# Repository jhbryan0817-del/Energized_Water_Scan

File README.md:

# Energized Water Scanner USV

A small unmanned surface vessel for research into detecting and mapping electrical hazards in flooded areas. Two deployable electrodes, E2/E4, measure voltage difference; the vessel must combine that measurement with validated probe pose, orientation and location. A low reading cannot establish that water is safe.

## Current state — 4 October 2026

**Electronics: Rev H engineering prototype. Mechanical assembly: live Fusion Rev I.** The PCB retains the 91 × 124 mm U-shaped perimeter, 58 × 48 mm motor opening, four mounting holes and 2 mm thickness. Six copper layers accommodate the revised electronics. The live Fusion assembly has been updated for Rev H placement, hull cleanup and corrective closure of obsolete bow/stern openings. Repository 3D exports remain historical; this update contains documentation and BOM changes only. See the [CAD audit](docs/CAD_Audit_2026-10-04.md) for verified results and remaining holds.

- [PCB design, operating limits and assembly](pcb/RevH/README.md)
- [Editable KiCad project](pcb/RevH/EWS_RevH.kicad_pro), [schematic PDF](pcb/RevH/EWS_RevH_schematic.pdf), [PCB BOM](pcb/RevH/BOM.csv), [connector pin map](pcb/RevH/PIN_MAP.md)
- [System design](docs/Design.md), [assembly and procurement](docs/Wiring_and_Assembly.md), [remaining qualification work](docs/Build_Qualification.md)
- [System BOM](BOM.csv): mechanical/harness items plus one assembled carrier. Components on that carrier are listed only in its PCB BOM.

Rev H adds a dedicated ADC per voltage range, hard-wired diagnostic/ready signals, reverse-input protection, a PCB-branch fuse and transient suppressor, battery monitoring and a dry-compartment ingress-sensor interface. The circuit targets sensitive measurements and a separate 600 V RMS, 50/60 Hz fault range. These are unqualified design targets. Bench calibration, insulation/protection review, physical fault testing and environmental qualification remain open. No validated acquisition firmware is supplied.

Historical Rev G previews and 3D exports are not the current mechanical authority. Use the saved live `Energized_Water_Scanner` Fusion document.

Two electrodes provide one field projection, not a full 3D field map or a direct measurement of floodwater current. Current-density estimates require independently measured conductivity and a valid field/geometry model. Fast transient measurement and an electrical-safety clearance decision are not released capabilities.

## Next milestones

1. Review the new PCB and validate components, protection, calibration, acquisition timing and fault behavior on a controlled bench.
2. Resolve the remaining mechanical holds in the CAD audit; verify actual components, wiring, seal compression and assembly tolerances.
3. Resolve actuator hardware and sealing, then test the unpowered hull for leakage and loaded flotation.
4. Implement and validate acquisition, invalid-state handling, pose/location logging and mapping; obtain appropriate laboratory qualification before hazardous exposure.

Detailed revision narratives and superseded preview images have been removed from the current documentation; Git history preserves them. Existing exported CAD releases are unchanged and superseded by the live Fusion assembly for this iteration. The `pcb/RevG` files are retained as the historical electrical baseline; use Rev H for new electronics work. Historical scripts and verification records retain their original scope and must not be treated as current acceptance evidence.

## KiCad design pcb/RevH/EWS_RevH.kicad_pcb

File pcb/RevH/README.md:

# Energized Water Scanner — PCB Rev H

**Engineering prototype, 3 October 2026.** Native KiCad 10 sources for the two-electrode flood-hazard research USV. Open `EWS_RevH.kicad_pro`. This revision changes electronics only. A subsequent 4 October live Fusion Rev I iteration updates the mechanical fit representation; see [CAD audit](../../docs/CAD_Audit_2026-10-04.md). No new STEP, F3D or STL was generated.

## What changed

- U4 at I2C address **0x48** acquires the high range. New U7 at **0x49** acquires the sensitive range. Both use AIN0–AIN1; each can run continuously at 860 samples/s nominal without alternating ranges. Their clocks are independent, so this is concurrent acquisition, not phase-synchronous sampling.
- Amplifier diagnostics and conversion-ready signals are routed to ESP32 inputs. No diagnostic fly-wires are needed. The existing expansion header still exposes these nets, but they are now reserved.
- J11 feeds F1, then a P-channel reverse-polarity MOSFET Q1. D5 suppresses positive transients on protected VBAT; D6 limits gate-source voltage. Added local rail capacitors supplement the regulator modules.
- A filtered 200 kΩ/33 kΩ battery divider, with 10 kΩ series and 100 nF at GPIO32, feeds ADC1 GPIO32. Its nominal ratio is 7.0606:1 (1.190 V at an 8.4 V battery), with an approximately 41.5 Hz pole. Select and calibrate the ESP32 ADC attenuation accordingly. J14 supports a dry-compartment, 3.3 V, open-drain ingress sensor on GPIO23. This is a powered sensor interface, not a pair of bare-water electrodes.
- Existing high-voltage divider networks, isolation packages, antenna restriction, U-shaped perimeter, motor opening and mounting holes are retained. The schematic, BOM and connector map describe the same board.

## Measurement capability and limits

E2 and E4 measure **signed differential voltage** along one probe separation. The DC-coupled analog circuit also permits AC measurements; initial AC qualification is for 50/60 Hz. These electrodes do not measure total current in floodwater. Under a validated locally uniform field model, the projected field is approximately `E_parallel = V / separation`. Estimating current density further requires conductivity, `J = conductivity × E`; total current also requires a defined area and field distribution. No conductivity sensor is included in this board. Use an independently isolated conductivity instrument if that quantity is needed; the ordinary I2C header is not an isolation barrier.

Two probes can miss a field perpendicular to their separation. A scan must include validated changes in orientation, accurate pose/time/location, immersion verification and invalid-data handling. Position/heading sensors can use the available 3.3 V I2C/UART interfaces; they are not fitted by this revision. DC electrode polarization, electrode material, fouling, contact impedance and motion-generated signals must be characterized separately from electronic DC response.

| Property | High range | Sensitive range |
|---|---:|---:|
| Series resistance per electrode leg | 4 × 249 kΩ | 4 × 249 kΩ |
| Sense resistance per leg | 1 kΩ | 100 kΩ |
| Ideal attenuation before isolation | 997:1 | 10.96:1 |
| Isolation-amplifier differential gain | 2 | 2 |
| Initial measurement target | 600 V RMS, 50/60 Hz; ±850 V DC engineering ceiling | ±2 V instantaneous |
| Initial ADS1115 PGA | ±2.048 V | ±0.512 V |
| Ideal electrode-referred code step | 31.16 mV | 85.63 µV |

These are design calculations, **not demonstrated accuracy, detection thresholds or exposure ratings**. The DC ceiling gives approximately the same divider stress as the crest of the AC target; continuous DC and wet electrochemistry still require separate validation. The low range intentionally clamps during a large fault. Do not use it until recovery has been characterized. PGA changes cannot recover a clipped amplifier signal or improve the amplifier's input offset.

Each differential ADC filter is 1 kΩ + 1 kΩ with 330 nF across the inputs: ideal pole 241 Hz. The ideal analog amplitude factors are approximately 0.979 at 50 Hz and 0.970 at 60 Hz. Include ADC digital-filter response, source loading, capacitor tolerance and temperature in calibration. Neither this pole nor the converter establishes broadband anti-alias performance. Fast impulses, arbitrary inverter spectra and high-frequency hazard characterization are not released capabilities.

At 600 V RMS, the ideal high-range AMC input is 0.851 V peak; its outputs remain approximately 0.589–2.291 V around the nominal 1.44 V common mode. Normal divider dissipation is about 22.5 mW per 249 kΩ resistor. Both channels together load the electrodes by about 1.044 MΩ before clamping and approximately 1 MΩ in a large fault. The source/electrode impedance can therefore produce substantial loading error. Per-resistor working voltage does not establish pulse withstand or a single-fault rating.

The AMC3330's specified input offset alone corresponds to about 0.299 V high-range or 3.29 mV sensitive-range electrode-referred error before calibration. Bias-current mismatch, clamp leakage, resistor matching, temperature and electrode effects add further error. A fine ADC code step is not proof of microvolt detection. Validate range overlap and retain separate calibration coefficients.

## Pin assignments

See [PIN_MAP.md](PIN_MAP.md) and `PIN_MAP.csv` for every connector pin.

| ESP32 GPIO | Rev H use |
|---|---|
| 36, input only | U4 high-range READY, active low; configure ADC conversion-ready mode |
| 35, input only | U7 sensitive-range READY, active low |
| 34, input only | U2 high-range DIAG, active low |
| 39, input only | U3 sensitive-range DIAG, active low |
| 32 / ADC1 | Battery health divider; calibrate ADC attenuation and gain |
| 23 | J14 ingress-sensor input; 10 kΩ pull-up, 1 kΩ series, 100 nF filter |
| 21 / 22 | SDA / SCL, 3.3 V I2C; addresses 0x48 and 0x49 reserved |
| 25 / 26 / 27 / 14 | E2 servo / E4 servo / steering / ESC control |

ADC AIN2 and AIN3 are grounded on each converter. They can support an occasional zero-input diagnostic during a deliberately invalidated acquisition interval. They are not available as general external analog inputs. J4 exposes both isolated-side analog pairs for service, and high READY/DIAG nets; low READY is also on J1 pin 6. Never connect anything on the floating electrode side to J4 or logic ground.

## Power and assembly

Use a **2S battery only**, 8.4 V maximum normal input. An external branch fuse near the battery remains necessary to protect its harness. F1 is a provisional 3 A fast fuse for the PCB branch; coordinate its interrupt rating and time-current curve with available fault current, inrush, connector ratings and measured loads. Motor/ESC propulsion current remains in its separate fused harness. F1 does not protect that harness.

Q1 is deliberately connected with **drain/tab to BAT_FUSED and source to protected VBAT**; reversing those connections defeats reverse-input blocking. At 2 A and the 10 mΩ room-temperature resistance limit quoted at −4.5 V gate drive, its calculated conduction loss is about 40 mW, before temperature increase. This is not a thermal qualification. It is not an ideal-diode controller and does not provide general backfeed isolation between powered sources.

D5 is a 12 V standoff SMBJ12A with a specified 19.9 V clamp at its rated test current. Actual overshoot, lead inductance, pulse energy and fuse coordination need testing. It is a battery-rail suppressor, not an electrode surge arrestor. Do not apply a sustained overvoltage or infer an automotive/load-dump rating. C40/C41/C42 are 25 V X5R parts; C41/C42 sit on 5 V outputs. Check effective capacitance under bias.

Keep combined servo load initially at or below the previous 2 A development limit, with a current-limited supply, and validate stall peaks and trace/via temperatures. Do not infer board current capacity from the D24V50F5 regulator name. New capacitors beneath U5/U6 require component height ≤1.35 mm and a measured ≥2 mm module standoff; check solder joints and module underside components too.

Disconnect the battery and remove JP1 before USB service. The ESP32 can be removed from its sockets. Battery monitoring is not an autonomous cell-balancing, undervoltage-cutoff or battery-management system. Do not leave the battery connected with the MCU supply deliberately removed: divider injection into an unpowered input has not been qualified. J14 is for short internal wiring to a compatible sensor; no exposed floodwater connection or external surge rating is provided. An absent sensor can resemble a dry condition and needs a pre-run functional check.

All GPIO are 3.3 V only. Retain a WROOM DevKitC V4. Flash pins remain unavailable; boot-strapping restrictions still apply to the remaining expansion pins. U5/U6 control pins at J9 are VIN-referenced, not direct GPIO interfaces. Leave the ESC BEC lead disconnected and insulated. Never parallel the regulator outputs.

## Mechanical interface

Six copper layers, 2 mm thickness, 91 × 124 mm overall. Fusion coordinates: X −20…71, Y −62…62 mm. Motor opening: X 13…71, Y −24…24 mm. Four Ø3.4 mm holes: (−17,−58.5), (67,−58.5), (−17,58.5), (67,58.5). KiCad X = Fusion X + 50; KiCad Y = 100 − Fusion Y.

Retain the Rev G 1 mm nylon spacer arrangement, subject to actual screw engagement and underside solder-tail clearance. The existing outline and hole geometry are checked against the previous board. Populated heights, leads, connectors, ESC attachment and hatch clearance must be checked in the next Fusion iteration and on real hardware. The populated fit representation is maintained only in the live Fusion document; it is not a supplier-certified assembly or a manufacturing export.

The nominal six-layer stack uses 70 µm outer and 35 µm inner copper, dielectric layers 0.20/0.30/0.70/0.30/0.20 mm, and 0.01 mm mask per side. It totals 2.00 mm. The fabricator must confirm materials, pressed thickness, tolerances and insulation requirements. No controlled impedance is claimed. The added layers provide space through the restricted neck without reducing the input-isolation rules.

## Verification and next work

**Final automated results: zero ERC violations, zero DRC violations, zero unrouted connections and zero schematic parity issues.** A separate schematic-netlist/board/manifest comparison matched 319 connected pins. Exact Edge.Cuts geometry and the four mounting holes match Rev G. `ERC.json`, `DRC.json`, `verification.json` and `calculations.json` record the checks actually performed. ERC/DRC cannot validate a circuit topology, component derating, electrode performance or electrical safety. Custom copper rules retain the prior 8 mm floating-input-to-logic target and graded internal divider spacing. They do not derive creepage, installation category, pollution degree, laminate CTI or wet-insulation compliance.

Before hazardous exposure, obtain a qualified insulation/protection review and laboratory verification of common-mode and differential exposure, surges, single faults, resistor failures, clamp leakage/recovery, humidity/contamination, dielectric withstand, lead/enclosure insulation and thermal limits. Establish actual sensitivity and calibrated bandwidth using isolated, current-limited laboratory sources. Do not test in occupied energized water. A low reading, broken lead, dry probe, stalled conversion or saturated channel must never be interpreted as safe water.

Firmware is deferred. Its contract is: configure both converters explicitly; timestamp each ready event; detect stale data, clipping, DIAG faults, startup and recovery; invalidate health failures; calculate DC and AC quantities separately; log pose/location and uncertainty. No minimum detectable field or alarm threshold is released.

## Primary references

- [TI AMC3330](https://www.ti.com/lit/ds/symlink/amc3330.pdf): isolated amplifier limits, input/output behavior and supply network.
- [TI ADS1115](https://www.ti.com/lit/ds/symlink/ads1115.pdf): PGA, MUX, I2C addressing and conversion-ready timing.
- [Diodes DMPH3010LK3](https://www.diodes.com/datasheet/download/DMPH3010LK3.pdf): MOSFET pinout and ratings.
- [Littelfuse SMBJ](https://m.littelfuse.com/~/media/electronics/datasheets/tvs_diodes/littelfuse_tvs_diode_smbj_datasheet.pdf.pdf) and [451/453 fuse series](https://www.littelfuse.com/~/media/electronics/datasheets/fuses/littelfuse_fuse_451_453_datasheet.pdf.pdf).
- [Espressif DevKitC V4](https://docs.espressif.com/projects/esp-dev-kits/en/latest/esp32/esp32-devkitc/user_guide.html), [Pololu logic module](https://www.pololu.com/product/2831), [Pololu servo module](https://www.pololu.com/product/2851).

Native files were edited through KiCad's pcbnew API and checked with kicad-cli 10.0.6. The local IPC server answered the version query but returned no open-document handler. No claim of live IPC board editing or physical testing is made.

The native schematic uses project-local functional pin-map symbols with named global nets, continuing the previous project style. It is electrically editable and checked for board parity; it is not a substitute for an independent circuit review. No new fabrication order or manufacturing release is authorized by these reports.

Checks use the configured project rules. The reports list inherited ignored checks, including missing courtyards, track-to-via centering and footprint filters. No new violation was excluded to obtain the result. Mechanical fit of parts above sockets or module standoffs remains a separate check. The archive intentionally excludes 3D models; references inherited from Rev G are represented in the live Fusion fit assembly, with provisional envelopes identified in the CAD audit.

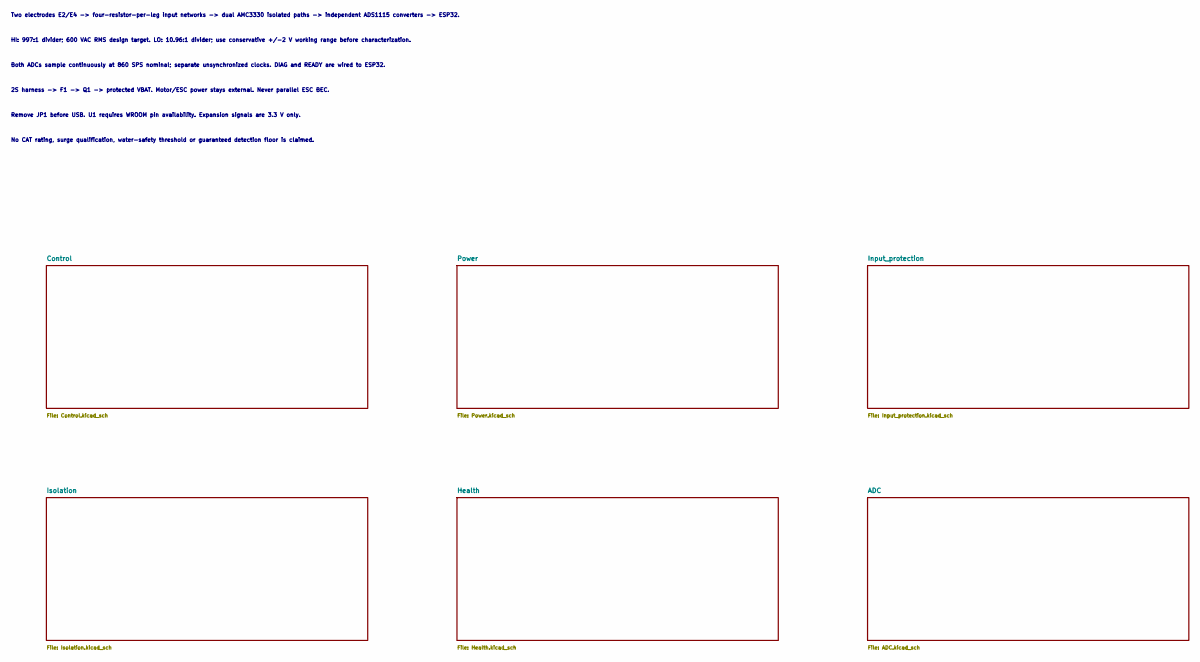
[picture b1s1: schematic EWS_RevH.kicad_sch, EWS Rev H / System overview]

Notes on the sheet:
Two electrodes E2/E4 -> four-resistor-per-leg input networks -> dual AMC3330 isolated paths -> independent ADS1115 converters -> ESP32.
HI: 997:1 divider; 600 VAC RMS design target. LO: 10.96:1 divider; use conservative +/-2 V working range before characterization.
Both ADCs sample continuously at 860 SPS nominal; separate unsynchronized clocks. DIAG and READY are wired to ESP32.
2S harness -> F1 -> Q1 -> protected VBAT. Motor/ESC power stays external. Never parallel ESC BEC.
Remove JP1 before USB. U1 requires WROOM pin availability. Expansion signals are 3.3 V only.
No CAT rating, surge qualification, water-safety threshold or guaranteed detection floor is claimed.

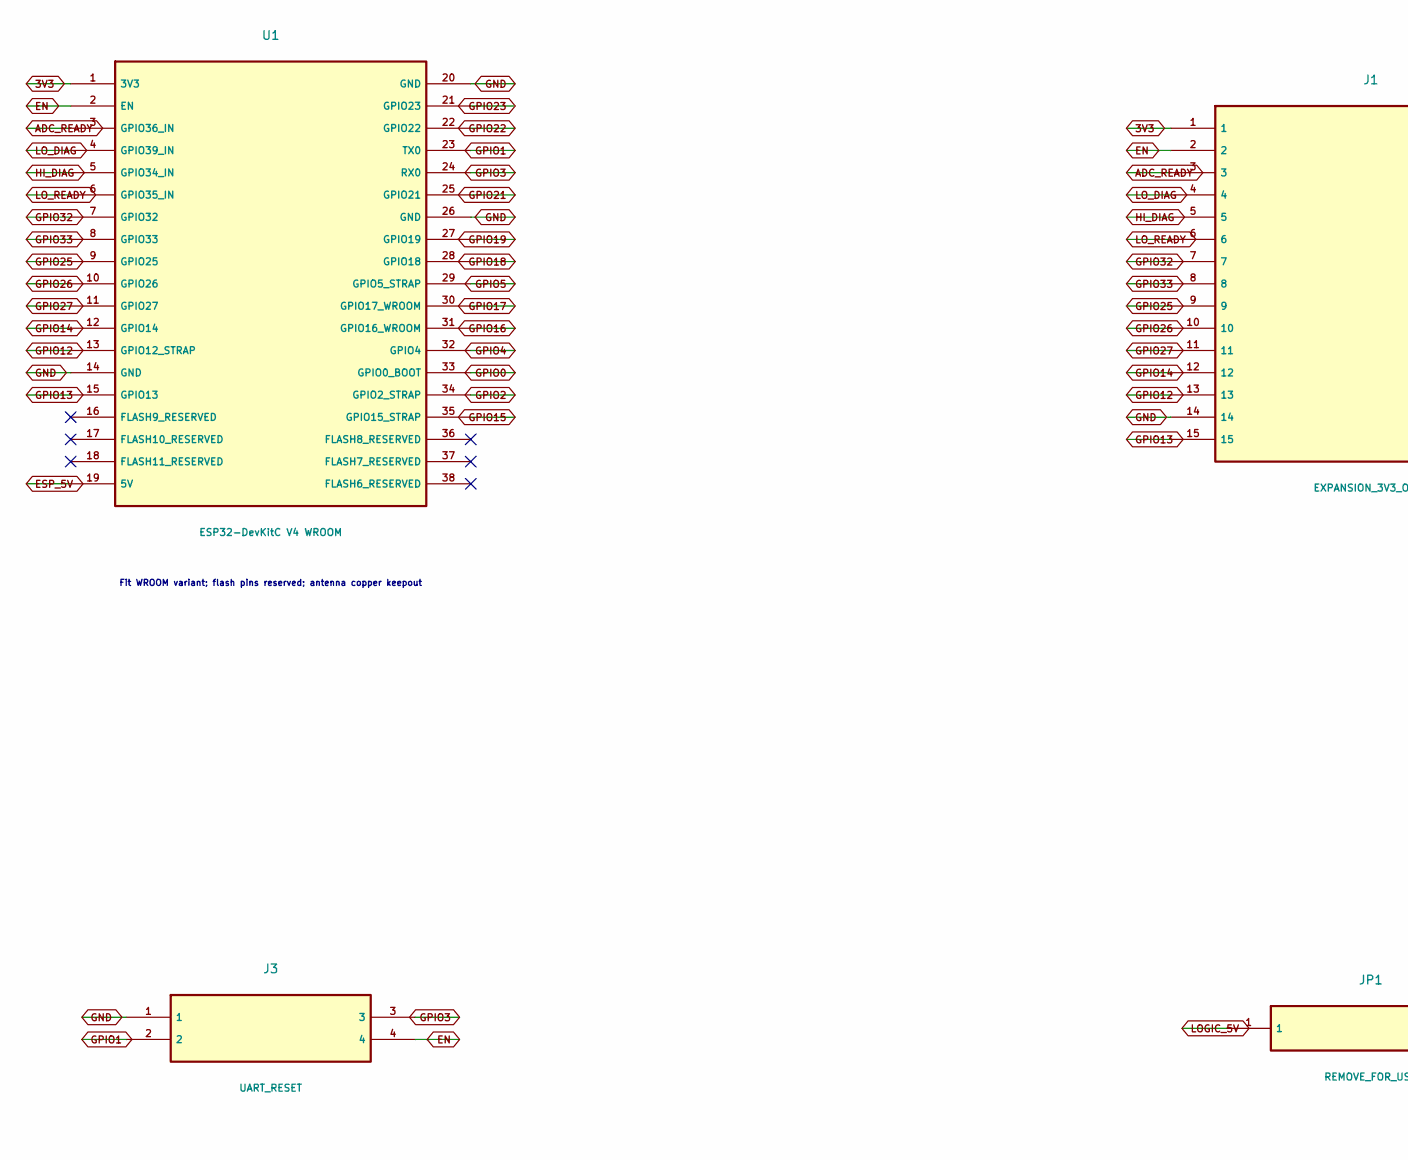
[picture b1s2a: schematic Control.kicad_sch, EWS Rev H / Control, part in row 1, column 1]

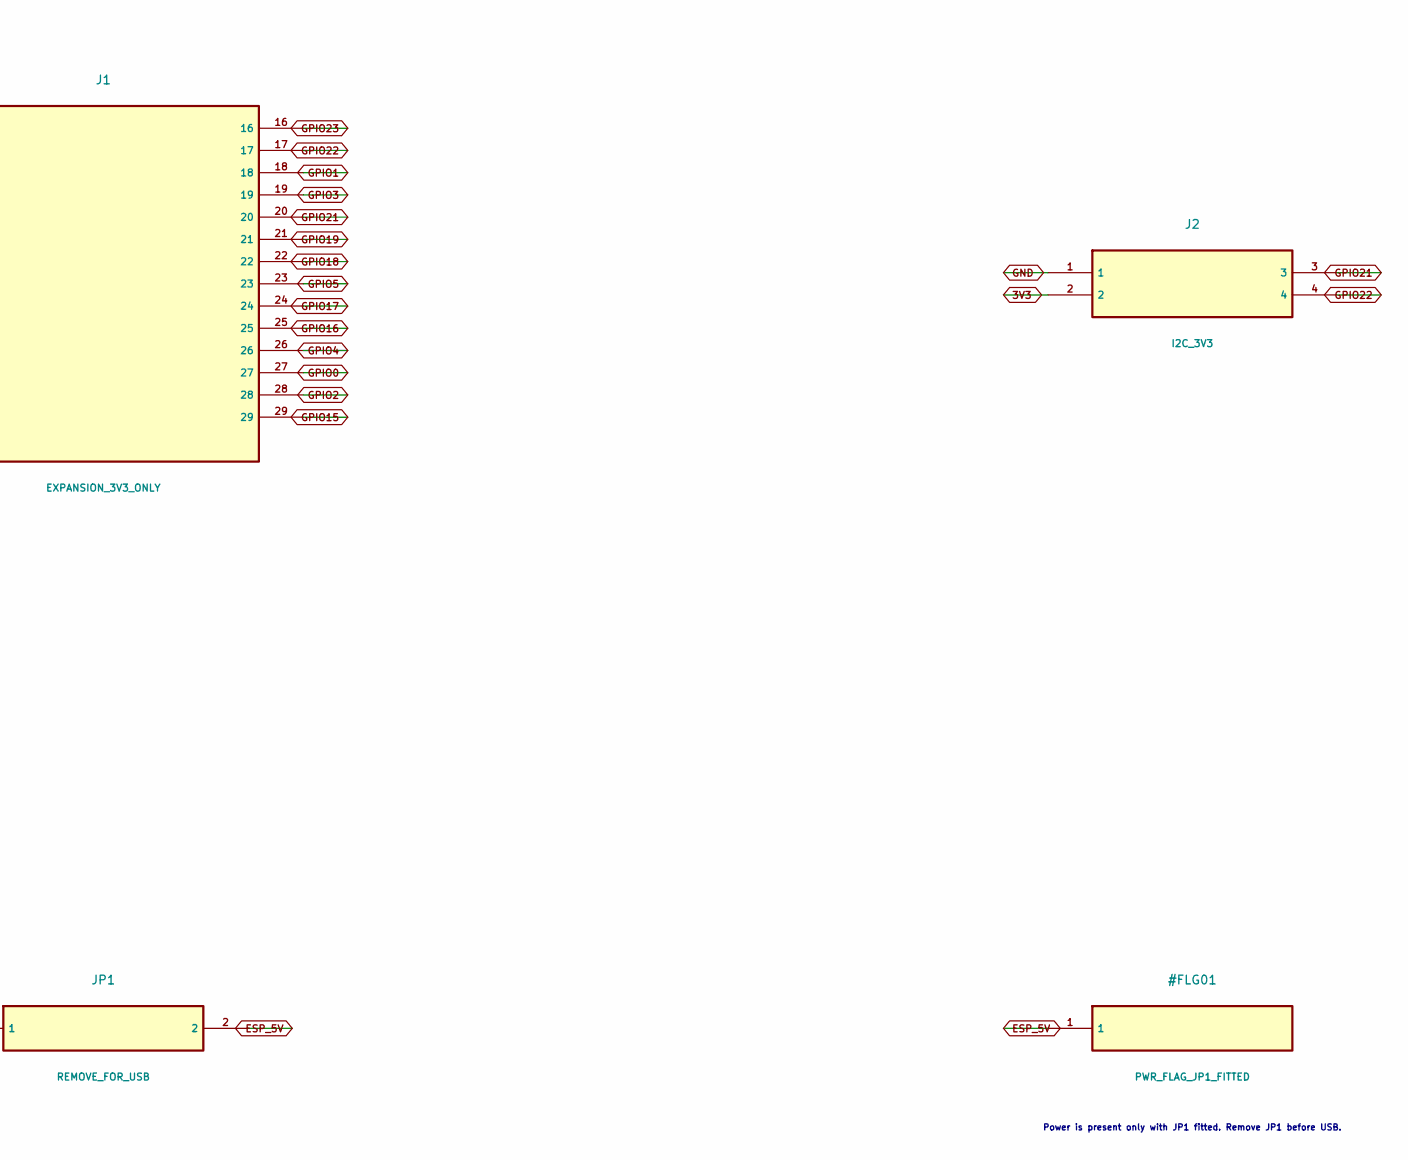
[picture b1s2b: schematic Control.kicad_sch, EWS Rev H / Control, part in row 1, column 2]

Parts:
J1: EXPANSION_3V3_ONLY; J1
J2: I2C_3V3; J2
J3: UART_RESET; J3
JP1: REMOVE_FOR_USB; JP1
U1: ESP32-DevKitC V4 WROOM; U1

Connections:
3V3: J1.1, J2.2, U1.1 (3V3); also elsewhere on the board
ADC_READY: J1.3, U1.3 (GPIO36_IN); also elsewhere on the board
EN: J1.2, J3.4, U1.2 (EN)
ESP_5V: JP1.2, U1.19 (5V)
GND: J1.14, J2.1, J3.1, U1.14 (GND), U1.20 (GND), U1.26 (GND); also elsewhere on the board
GPIO0: J1.27, U1.33 (GPIO0_BOOT)
GPIO1: J1.18, J3.2, U1.23 (TX0)
GPIO2: J1.28, U1.34 (GPIO2_STRAP)
GPIO3: J1.19, J3.3, U1.24 (RX0)
GPIO4: J1.26, U1.32 (GPIO4)
GPIO5: J1.23, U1.29 (GPIO5_STRAP)
GPIO12: J1.13, U1.13 (GPIO12_STRAP)
GPIO13: J1.15, U1.15 (GPIO13)
GPIO14: J1.12, U1.12 (GPIO14); also elsewhere on the board
GPIO15: J1.29, U1.35 (GPIO15_STRAP)
GPIO16: J1.25, U1.31 (GPIO16_WROOM)
GPIO17: J1.24, U1.30 (GPIO17_WROOM)
GPIO18: J1.22, U1.28 (GPIO18)
GPIO19: J1.21, U1.27 (GPIO19)
GPIO21: J1.20, J2.3, U1.25 (GPIO21); also elsewhere on the board
GPIO22: J1.17, J2.4, U1.22 (GPIO22); also elsewhere on the board
GPIO23: J1.16, U1.21 (GPIO23); also elsewhere on the board
GPIO25: J1.9, U1.9 (GPIO25); also elsewhere on the board
GPIO26: J1.10, U1.10 (GPIO26); also elsewhere on the board
GPIO27: J1.11, U1.11 (GPIO27); also elsewhere on the board
GPIO32: J1.7, U1.7 (GPIO32); also elsewhere on the board
GPIO33: J1.8, U1.8 (GPIO33)
HI_DIAG: J1.5, U1.5 (GPIO34_IN); also elsewhere on the board
LOGIC_5V: JP1.1; also elsewhere on the board
LO_DIAG: J1.4, U1.4 (GPIO39_IN); also elsewhere on the board
LO_READY: J1.6, U1.6 (GPIO35_IN); also elsewhere on the board

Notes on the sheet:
Fit WROOM variant; flash pins reserved; antenna copper keepout
Power is present only with JP1 fitted. Remove JP1 before USB.

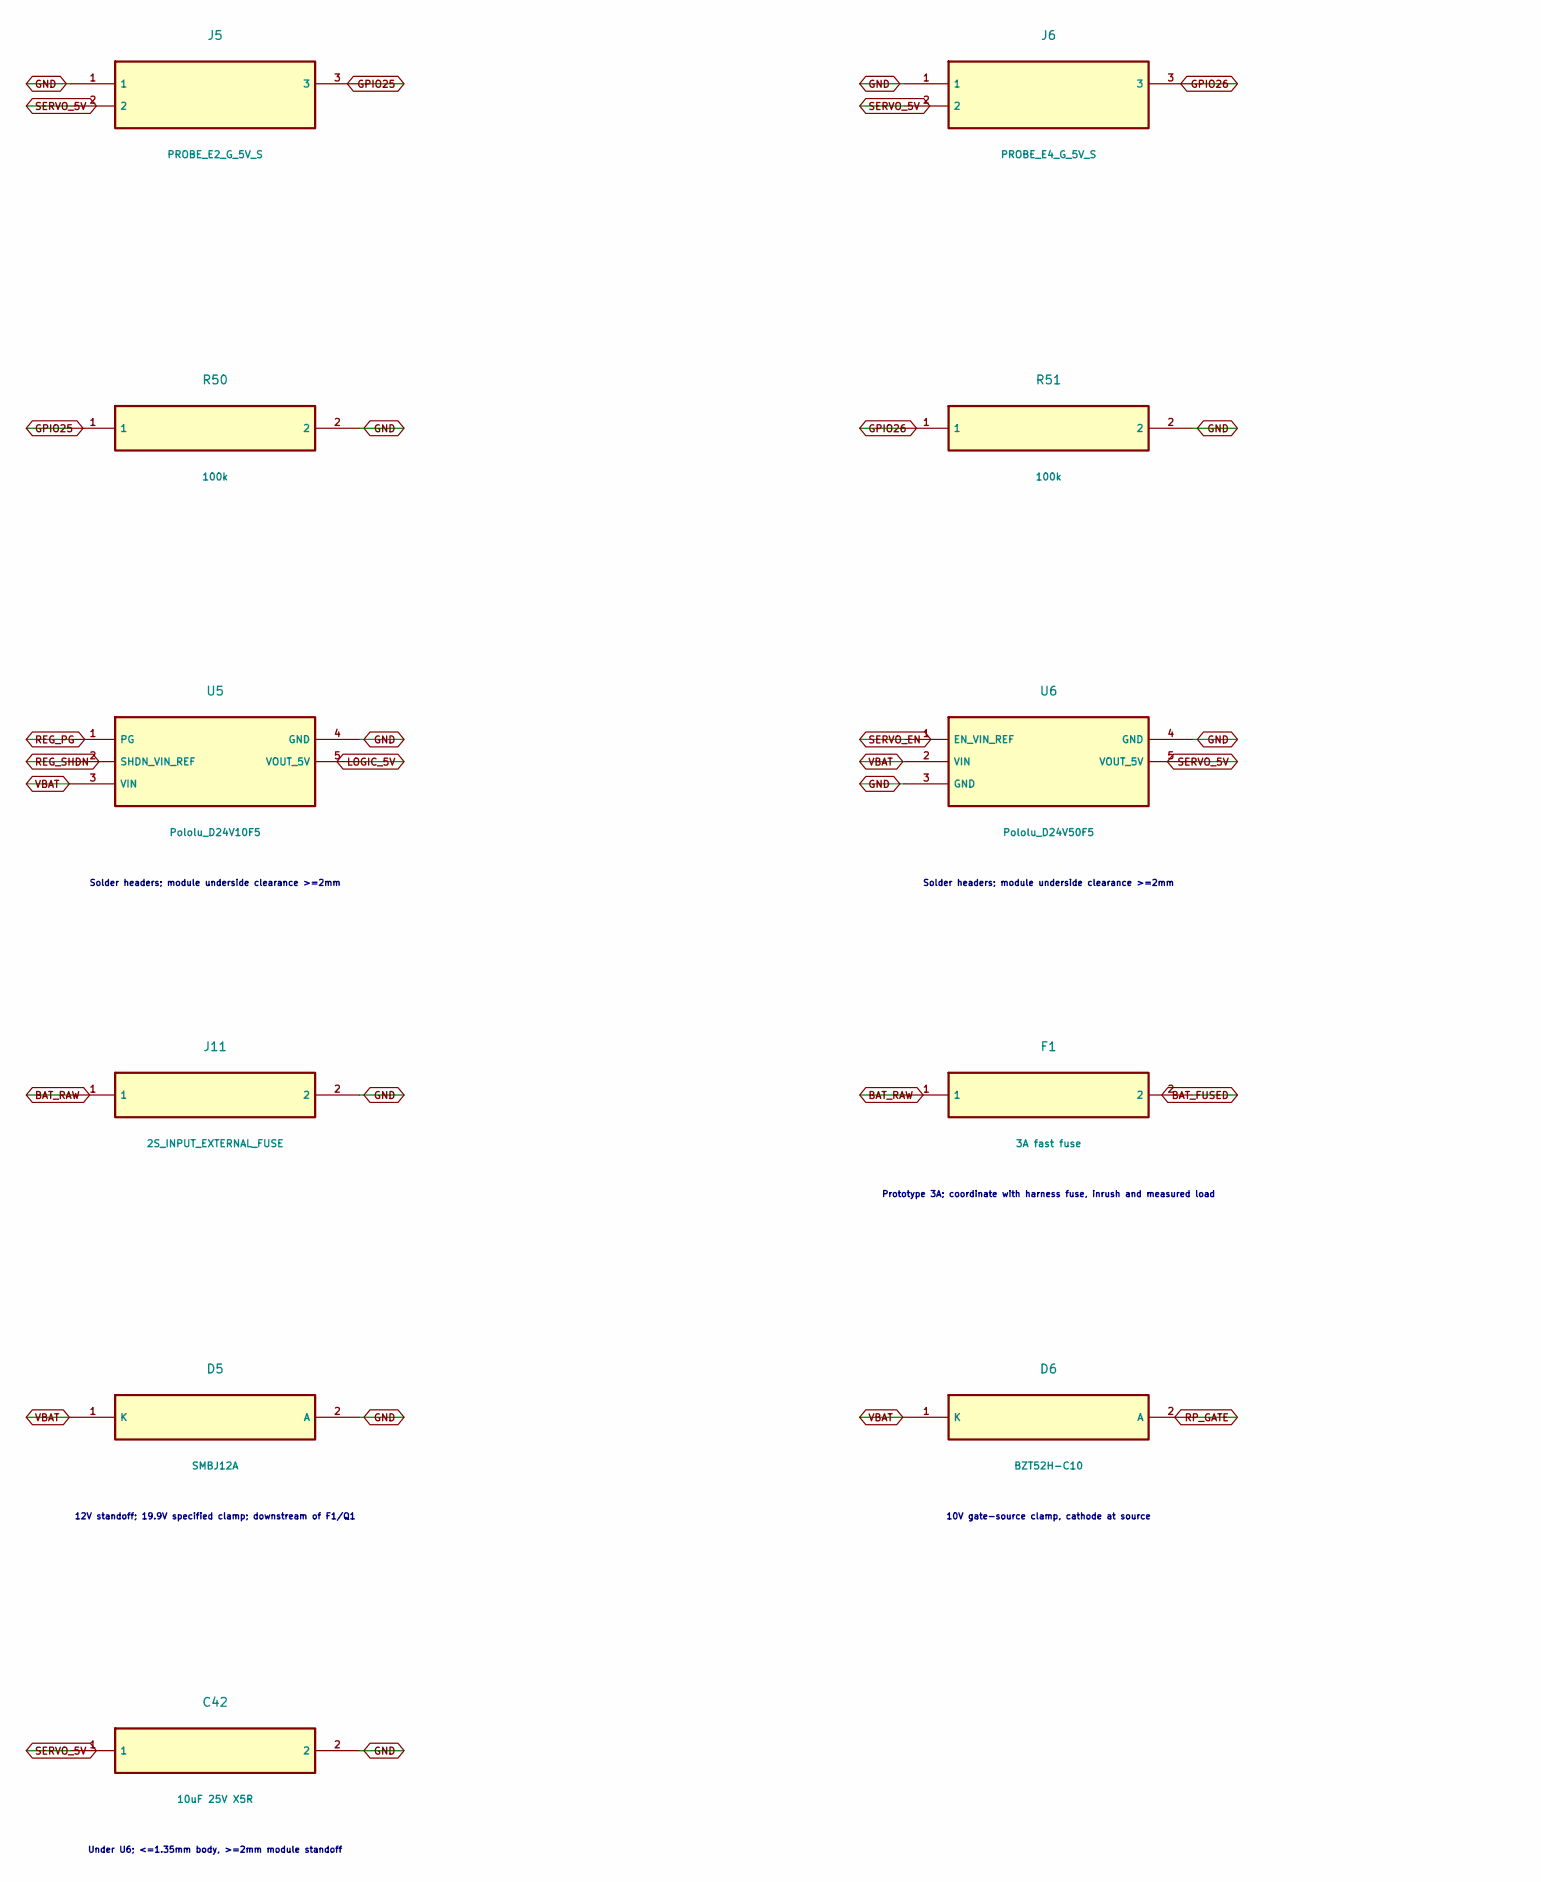
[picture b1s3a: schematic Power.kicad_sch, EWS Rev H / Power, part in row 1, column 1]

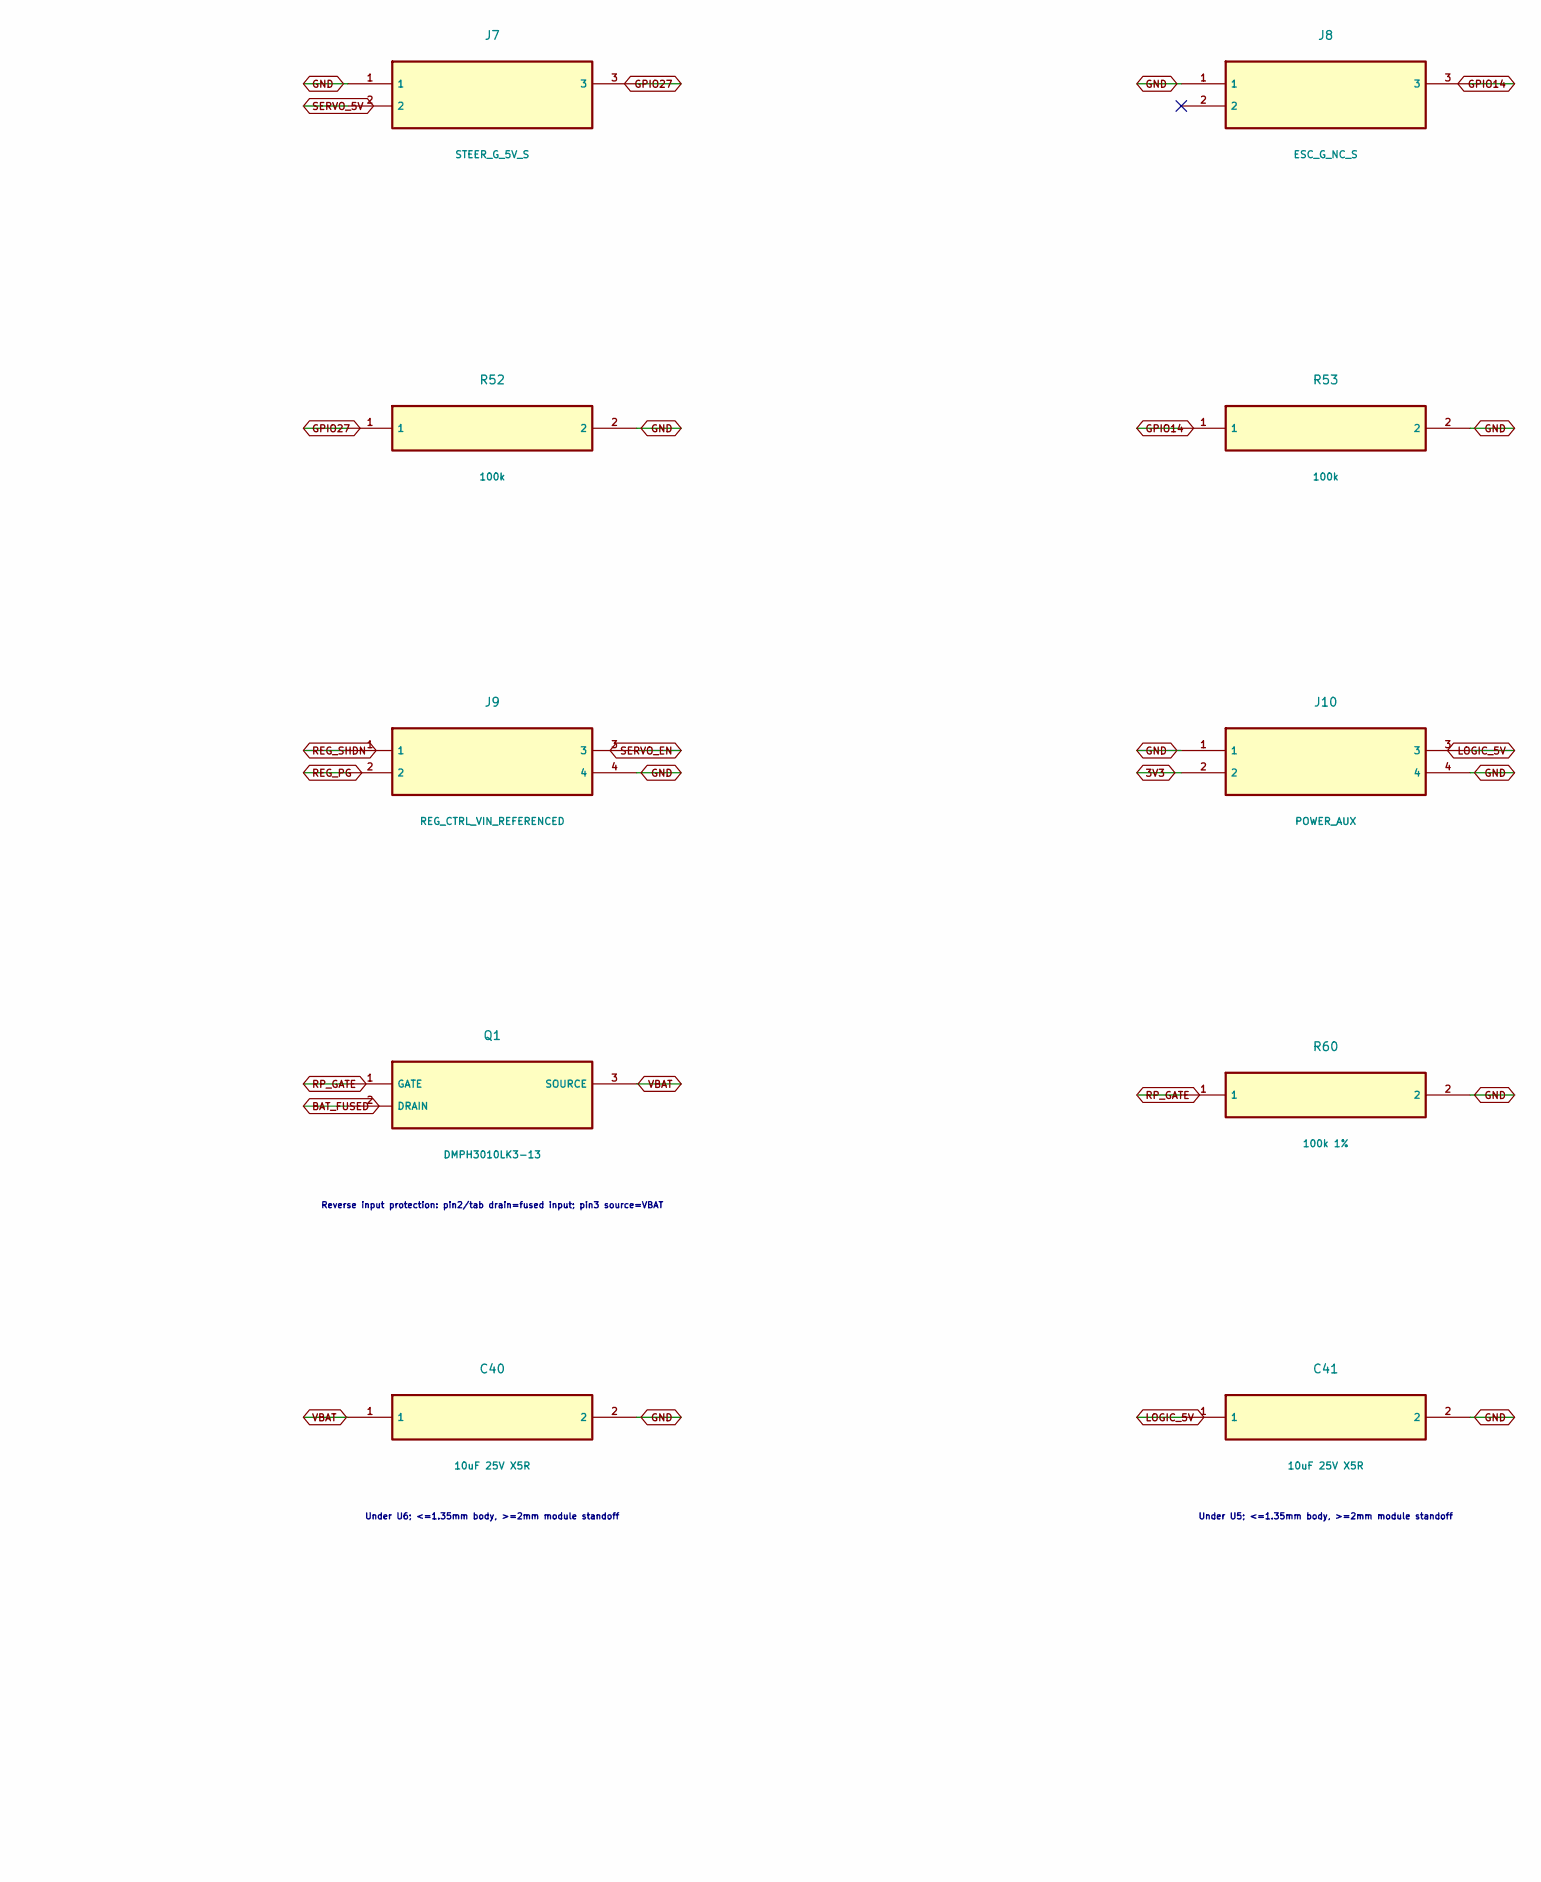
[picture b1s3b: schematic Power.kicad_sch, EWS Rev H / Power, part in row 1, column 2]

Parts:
C40: 10uF 25V X5R; C40
C41: 10uF 25V X5R; C41
C42: 10uF 25V X5R; C42
D5: SMBJ12A; D5
D6: BZT52H-C10; D6
F1: 3A fast fuse; F1
J5: PROBE_E2_G_5V_S; J5
J6: PROBE_E4_G_5V_S; J6
J7: STEER_G_5V_S; J7
J8: ESC_G_NC_S; J8
J9: REG_CTRL_VIN_REFERENCED; J9
J10: POWER_AUX; J10
J11: 2S_INPUT_EXTERNAL_FUSE; J11
Q1: DMPH3010LK3-13; Q1
R50: 100k; R50
R51: 100k; R51
R52: 100k; R52
R53: 100k; R53
R60: 100k 1%; R60
U5: Pololu_D24V10F5; U5
U6: Pololu_D24V50F5; U6

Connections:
3V3: J10.2; also elsewhere on the board
BAT_FUSED: F1.2, Q1.2 (DRAIN)
BAT_RAW: F1.1, J11.1
GND: C40.2, C41.2, C42.2, D5.2 (A), J5.1, J6.1, J7.1, J8.1, J9.4, J10.1, J10.4, J11.2, R50.2, R51.2, R52.2, R53.2, R60.2, U5.4 (GND), U6.3 (GND), U6.4 (GND); also elsewhere on the board
GPIO14: J8.3, R53.1; also elsewhere on the board
GPIO25: J5.3, R50.1; also elsewhere on the board
GPIO26: J6.3, R51.1; also elsewhere on the board
GPIO27: J7.3, R52.1; also elsewhere on the board
LOGIC_5V: C41.1, J10.3, U5.5 (VOUT_5V); also elsewhere on the board
REG_PG: J9.2, U5.1 (PG)
REG_SHDN: J9.1, U5.2 (SHDN_VIN_REF)
RP_GATE: D6.2 (A), Q1.1 (GATE), R60.1
SERVO_5V: C42.1, J5.2, J6.2, J7.2, U6.5 (VOUT_5V)
SERVO_EN: J9.3, U6.1 (EN_VIN_REF)
VBAT: C40.1, D5.1 (K), D6.1 (K), Q1.3 (SOURCE), U5.3 (VIN), U6.2 (VIN); also elsewhere on the board

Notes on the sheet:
Solder headers; module underside clearance >=2mm
Prototype 3A; coordinate with harness fuse, inrush and measured load
Reverse input protection: pin2/tab drain=fused input; pin3 source=VBAT
12V standoff; 19.9V specified clamp; downstream of F1/Q1
10V gate-source clamp, cathode at source
Under U6; <=1.35mm body, >=2mm module standoff
Under U5; <=1.35mm body, >=2mm module standoff

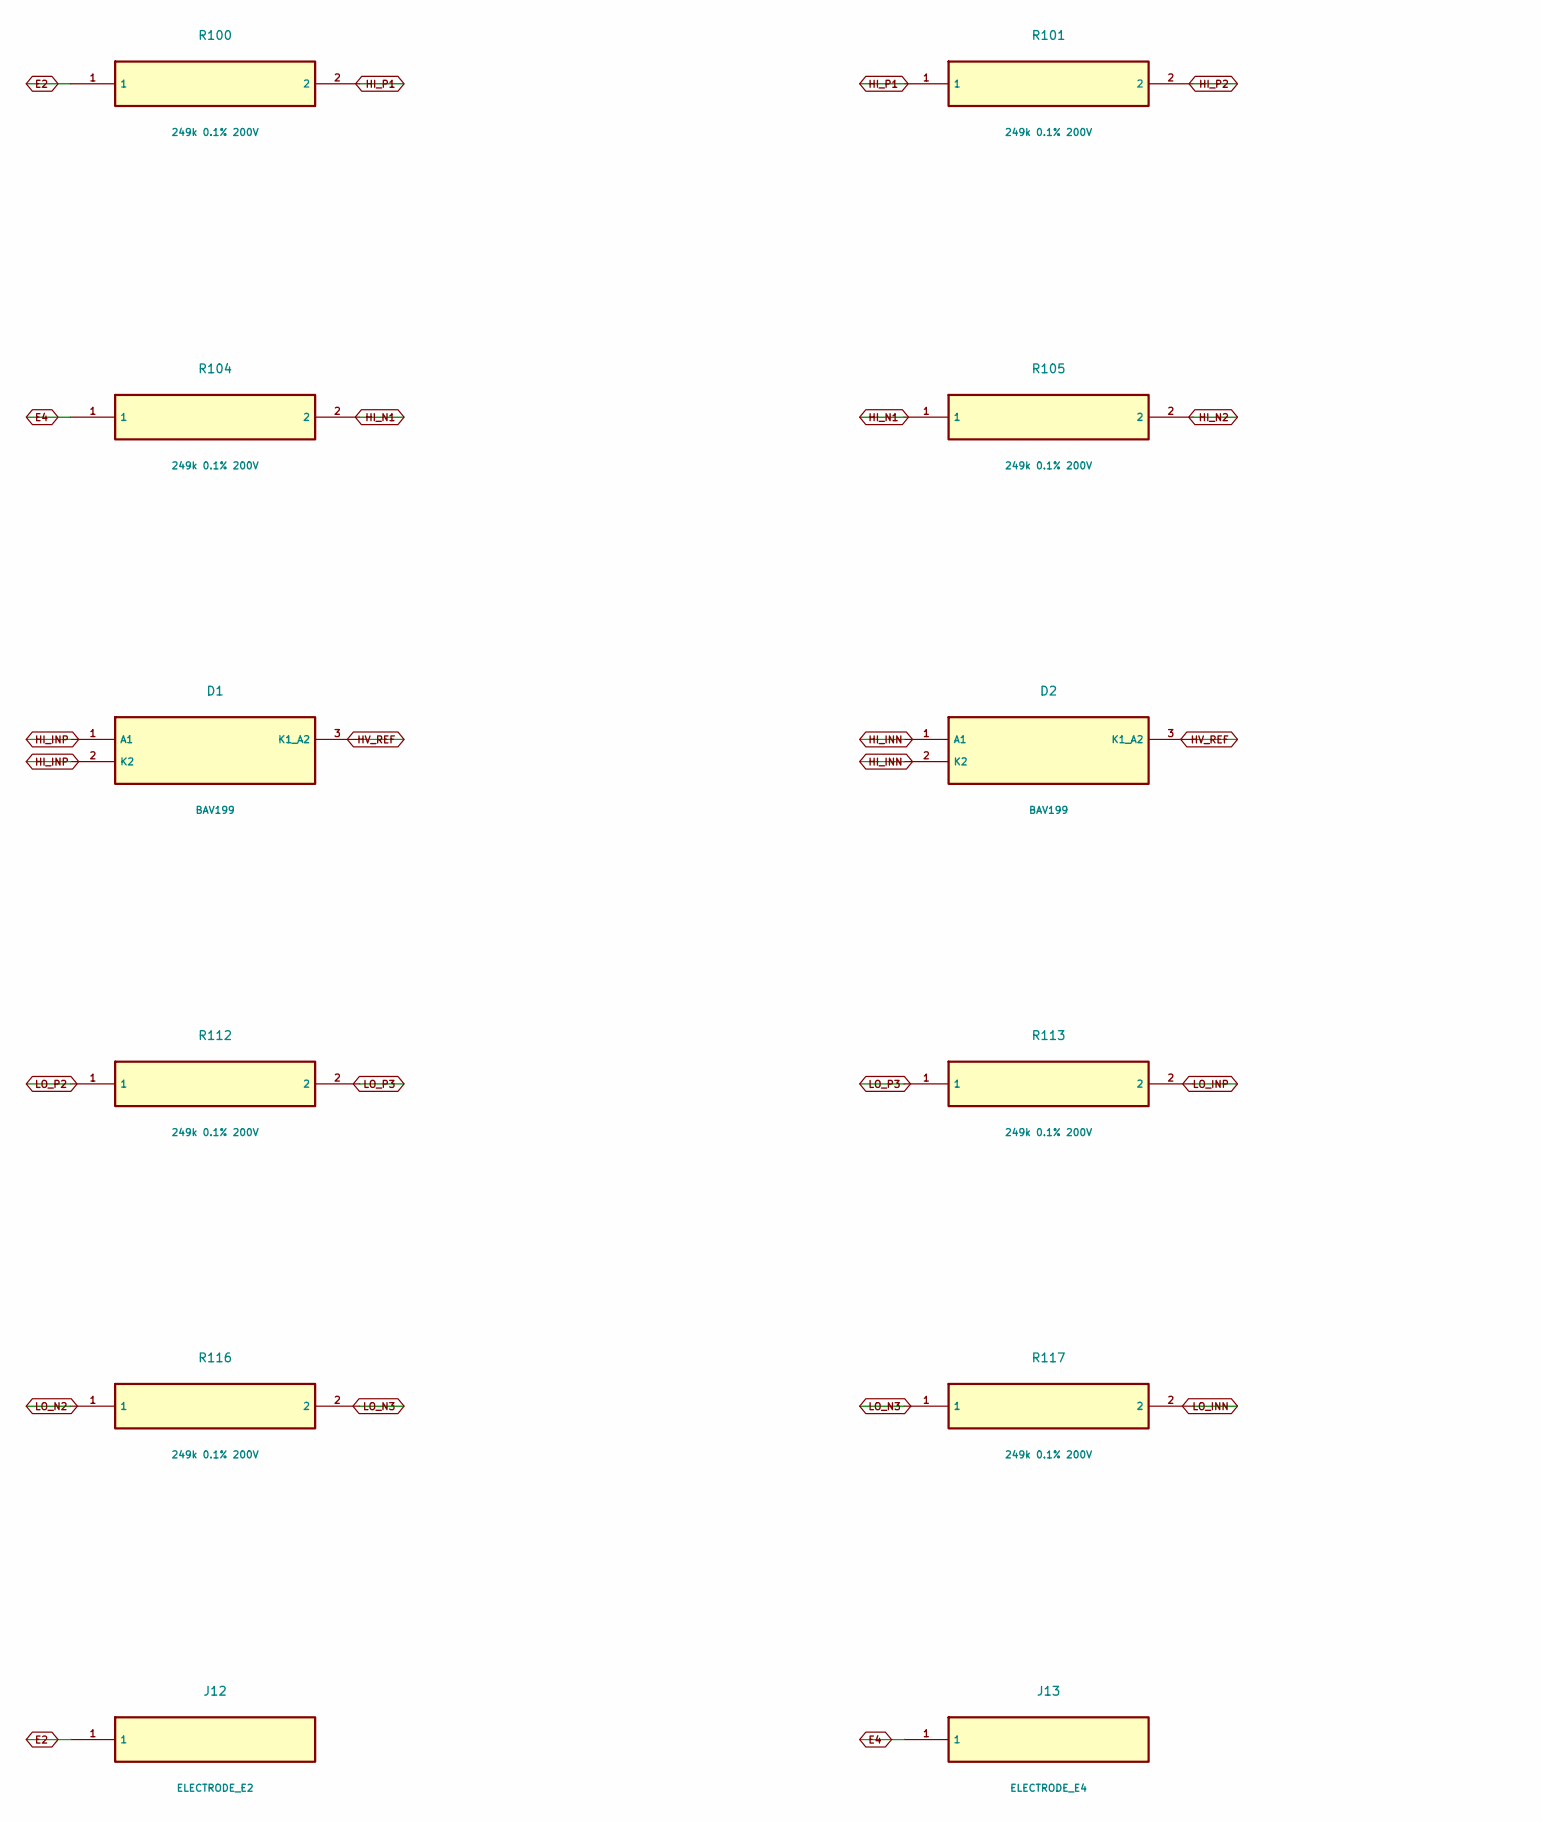
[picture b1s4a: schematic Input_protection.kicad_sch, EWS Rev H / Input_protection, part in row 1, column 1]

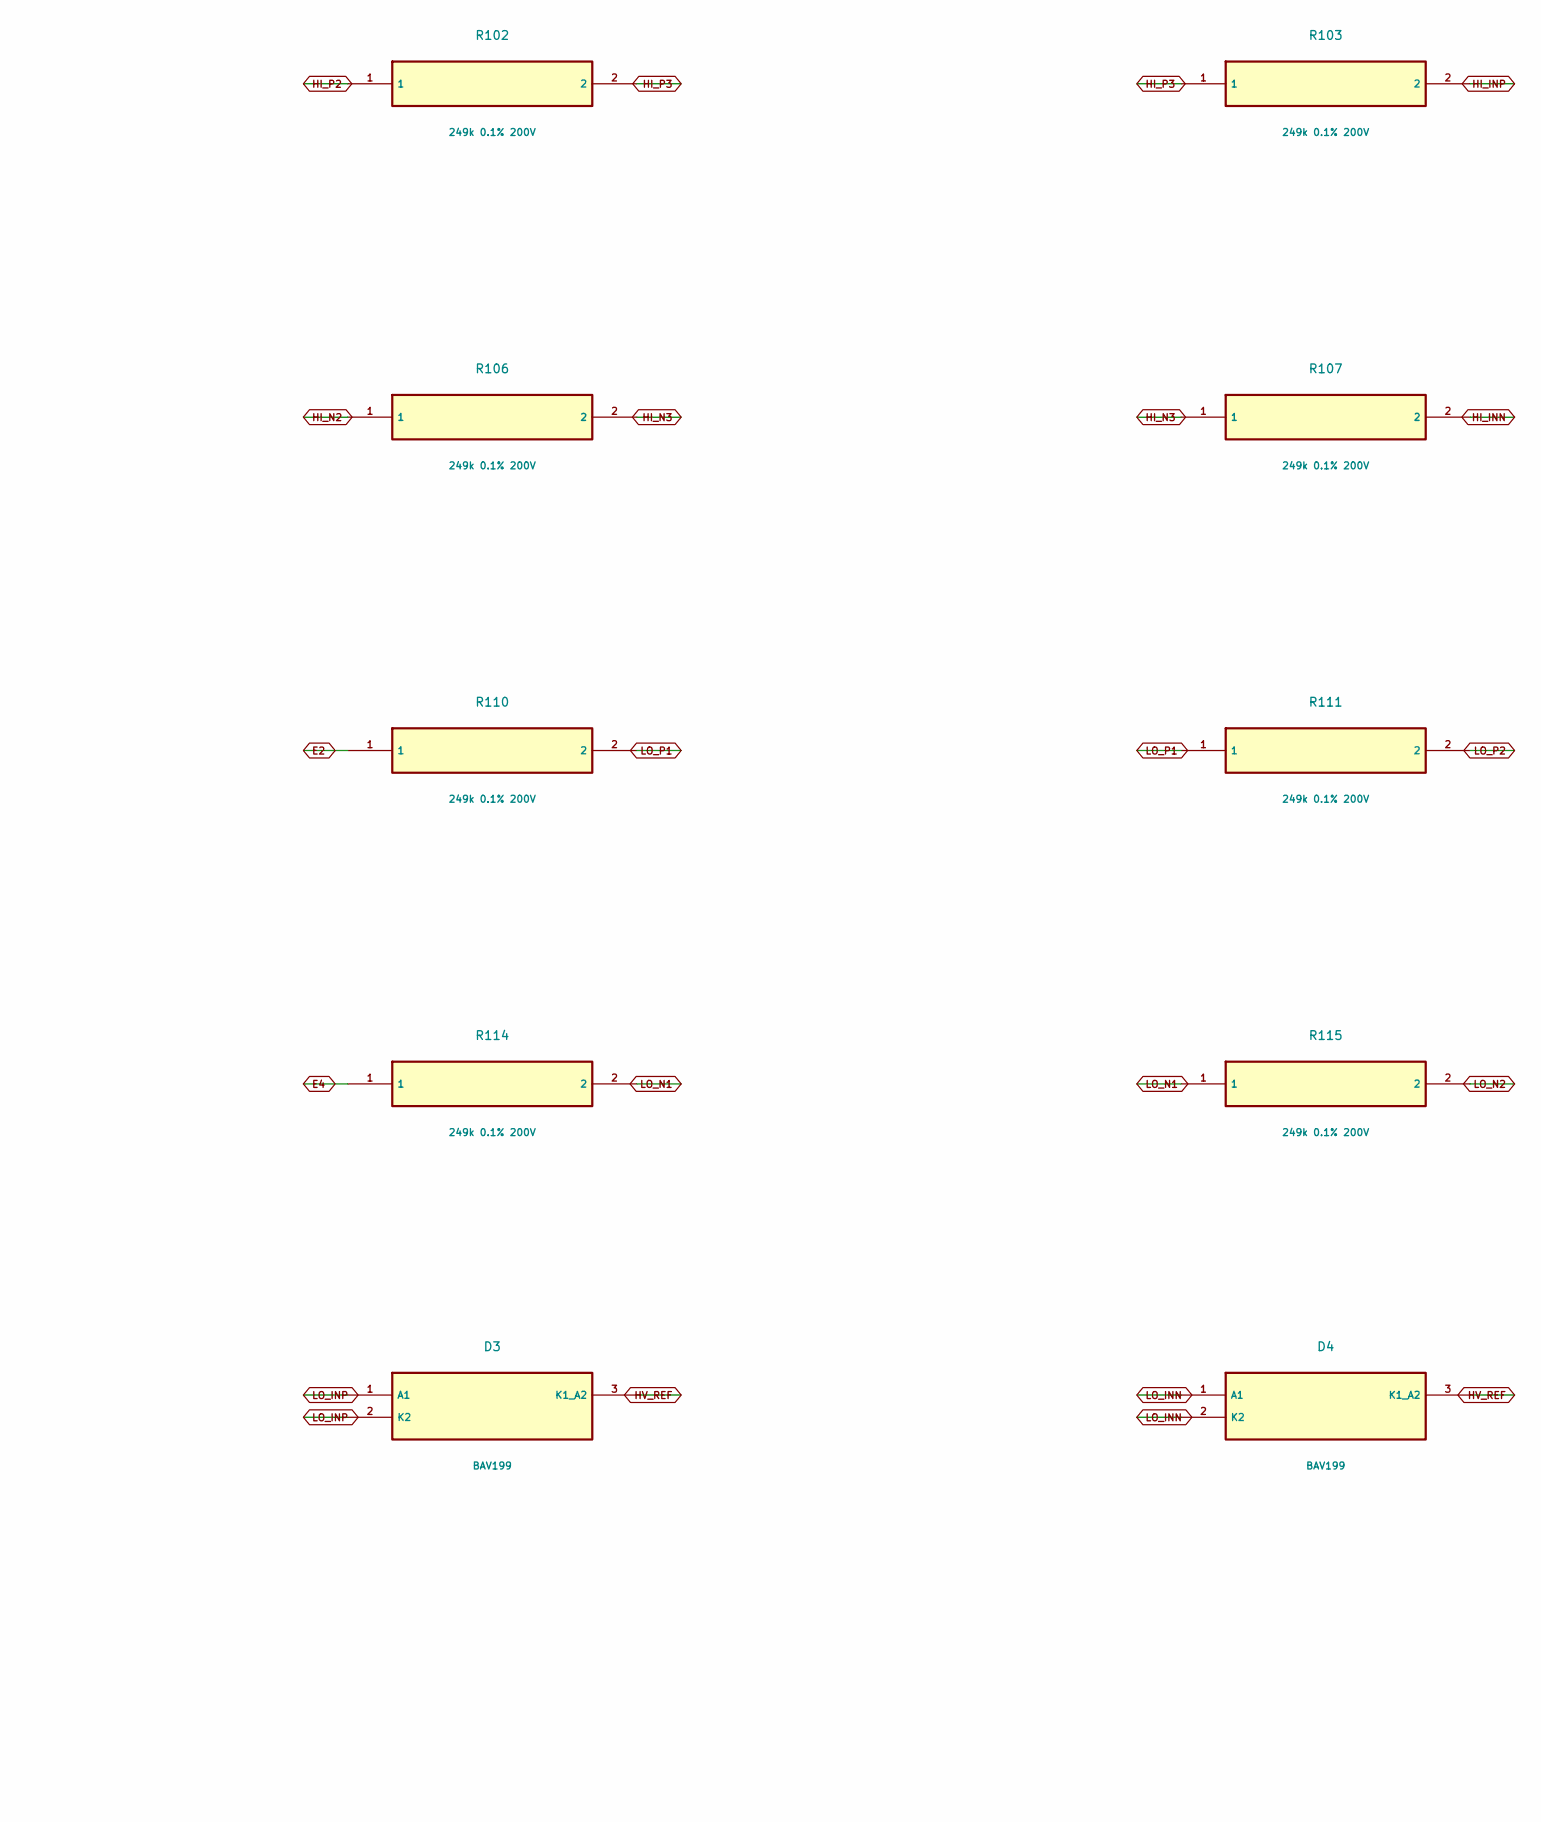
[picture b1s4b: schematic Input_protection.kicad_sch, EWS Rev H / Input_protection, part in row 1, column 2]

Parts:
D1: BAV199; D1
D2: BAV199; D2
D3: BAV199; D3
D4: BAV199; D4
J12: ELECTRODE_E2; J12
J13: ELECTRODE_E4; J13
R100: 249k 0.1% 200V; R100
R101: 249k 0.1% 200V; R101
R102: 249k 0.1% 200V; R102
R103: 249k 0.1% 200V; R103
R104: 249k 0.1% 200V; R104
R105: 249k 0.1% 200V; R105
R106: 249k 0.1% 200V; R106
R107: 249k 0.1% 200V; R107
R110: 249k 0.1% 200V; R110
R111: 249k 0.1% 200V; R111
R112: 249k 0.1% 200V; R112
R113: 249k 0.1% 200V; R113
R114: 249k 0.1% 200V; R114
R115: 249k 0.1% 200V; R115
R116: 249k 0.1% 200V; R116
R117: 249k 0.1% 200V; R117

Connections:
E2: J12.1, R100.1, R110.1
E4: J13.1, R104.1, R114.1
HI_INN: D2.1 (A1), D2.2 (K2), R107.2; also elsewhere on the board
HI_INP: D1.1 (A1), D1.2 (K2), R103.2; also elsewhere on the board
HI_N1: R104.2, R105.1
HI_N2: R105.2, R106.1
HI_N3: R106.2, R107.1
HI_P1: R100.2, R101.1
HI_P2: R101.2, R102.1
HI_P3: R102.2, R103.1
HV_REF: D1.3 (K1_A2), D2.3 (K1_A2), D3.3 (K1_A2), D4.3 (K1_A2); also elsewhere on the board
LO_INN: D4.1 (A1), D4.2 (K2), R117.2; also elsewhere on the board
LO_INP: D3.1 (A1), D3.2 (K2), R113.2; also elsewhere on the board
LO_N1: R114.2, R115.1
LO_N2: R115.2, R116.1
LO_N3: R116.2, R117.1
LO_P1: R110.2, R111.1
LO_P2: R111.2, R112.1
LO_P3: R112.2, R113.1
